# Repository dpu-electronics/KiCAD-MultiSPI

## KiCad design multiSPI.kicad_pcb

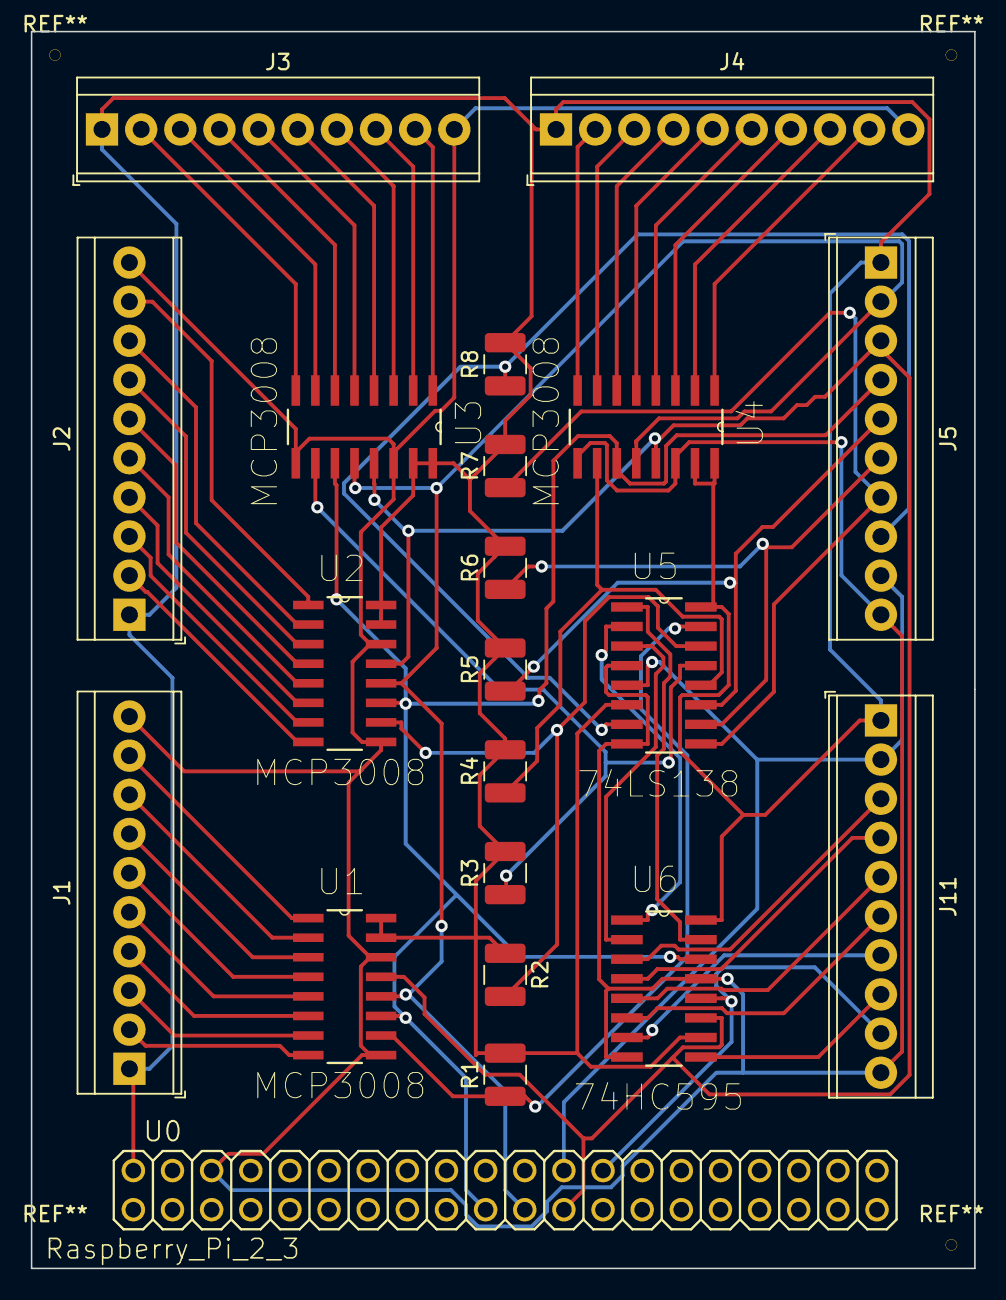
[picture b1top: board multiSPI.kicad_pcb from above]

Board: 2 copper layers, 61.2 x 80.3 mm, 21 parts (0 on the bottom side), 56 nets.

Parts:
J1, J2, J3, J4, J5, J11: Screw_Terminal_01x10; TerminalBlock_TE_1-282834-0_1x10_P2.54mm_Horizontal
R1, R2, R3, R4, R5, R6, R7, R8: 100k; R_1210_3225Metric
U0: Raspberry_Pi_2_3; 2X20
U1, U2, U3, U4: MCP3008; SOIC127P600X175-16N
U5: 74LS138; SOIC127P600X175-16N
U6: 74HC595; SOIC127P600X175-16N

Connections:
GND: J1.10, J2.10, J3.10, J4.10, J5.10, J11.10, U0.6, U1.9, U1.14, U2.9, U2.14, U3.9, U3.14, U4.9, U4.14, U5.4, U5.8, U6.8, U6.13
unnamed: J1.2, U1.8
unnamed: J1.3, U1.7
unnamed: J1.4, U1.6
unnamed: J1.5, U1.5
unnamed: J1.6, U1.4
unnamed: J1.7, U1.3
unnamed: J1.8, U1.2
unnamed: J1.9, U1.1
unnamed: J2.2, U2.8
unnamed: J2.3, U2.7
unnamed: J2.4, U2.6
unnamed: J2.5, U2.5
unnamed: J2.6, U2.4
unnamed: J2.7, U2.3
unnamed: J2.8, U2.2
unnamed: J2.9, U2.1
unnamed: J3.2, U3.8
unnamed: J3.3, U3.7
unnamed: J3.4, U3.6
unnamed: J3.5, U3.5
unnamed: J3.6, U3.4
unnamed: J3.7, U3.3
unnamed: J3.8, U3.2
unnamed: J3.9, U3.1
unnamed: J4.2, U4.8
unnamed: J4.3, U4.7
unnamed: J4.4, U4.6
unnamed: J4.5, U4.5
unnamed: J4.6, U4.4
unnamed: J4.7, U4.3
unnamed: J4.8, U4.2
unnamed: J4.9, U4.1
unnamed: J5.2, U0.21, U1.12, U2.12, U3.12, U4.12
unnamed: J5.3, U0.23, U1.13, U2.13, U3.13, U4.13, U6.11
unnamed: J5.4, U0.19, U1.11, U2.11, U3.11, U4.11, U6.14
unnamed: J5.5, R5.1, U5.11
unnamed: J5.6, R6.1, U5.10
unnamed: J5.7, R7.1, U5.9
unnamed: J5.8, R8.1, U5.7
unnamed: J5.9, J11.2, U0.24, U5.5
unnamed: J11.3, U6.3
unnamed: J11.4, U6.4
unnamed: J11.5, U6.5
unnamed: J11.6, U6.6
unnamed: J11.7, U6.7
unnamed: J11.8, U6.9
unnamed: J11.9, U0.26, U6.12
unnamed: R1.1, U1.10, U5.15
unnamed: R2.2, U2.10, U5.14
unnamed: R3.1, U3.10, U5.13
unnamed: R4.1, U4.10, U5.12
unnamed: U5.1, U6.15
unnamed: U5.2, U6.1
unnamed: U5.3, U6.2
VCC: J1.1, J2.1, J3.1, J4.1, J5.1, J11.1, R1.2, R2.1, R3.2, R4.2, R5.2, R6.2, R7.2, R8.2, U0.2, U1.15, U1.16, U2.15, U2.16, U3.15, U3.16, U4.15, U4.16, U5.6, U5.16, U6.10, U6.16
